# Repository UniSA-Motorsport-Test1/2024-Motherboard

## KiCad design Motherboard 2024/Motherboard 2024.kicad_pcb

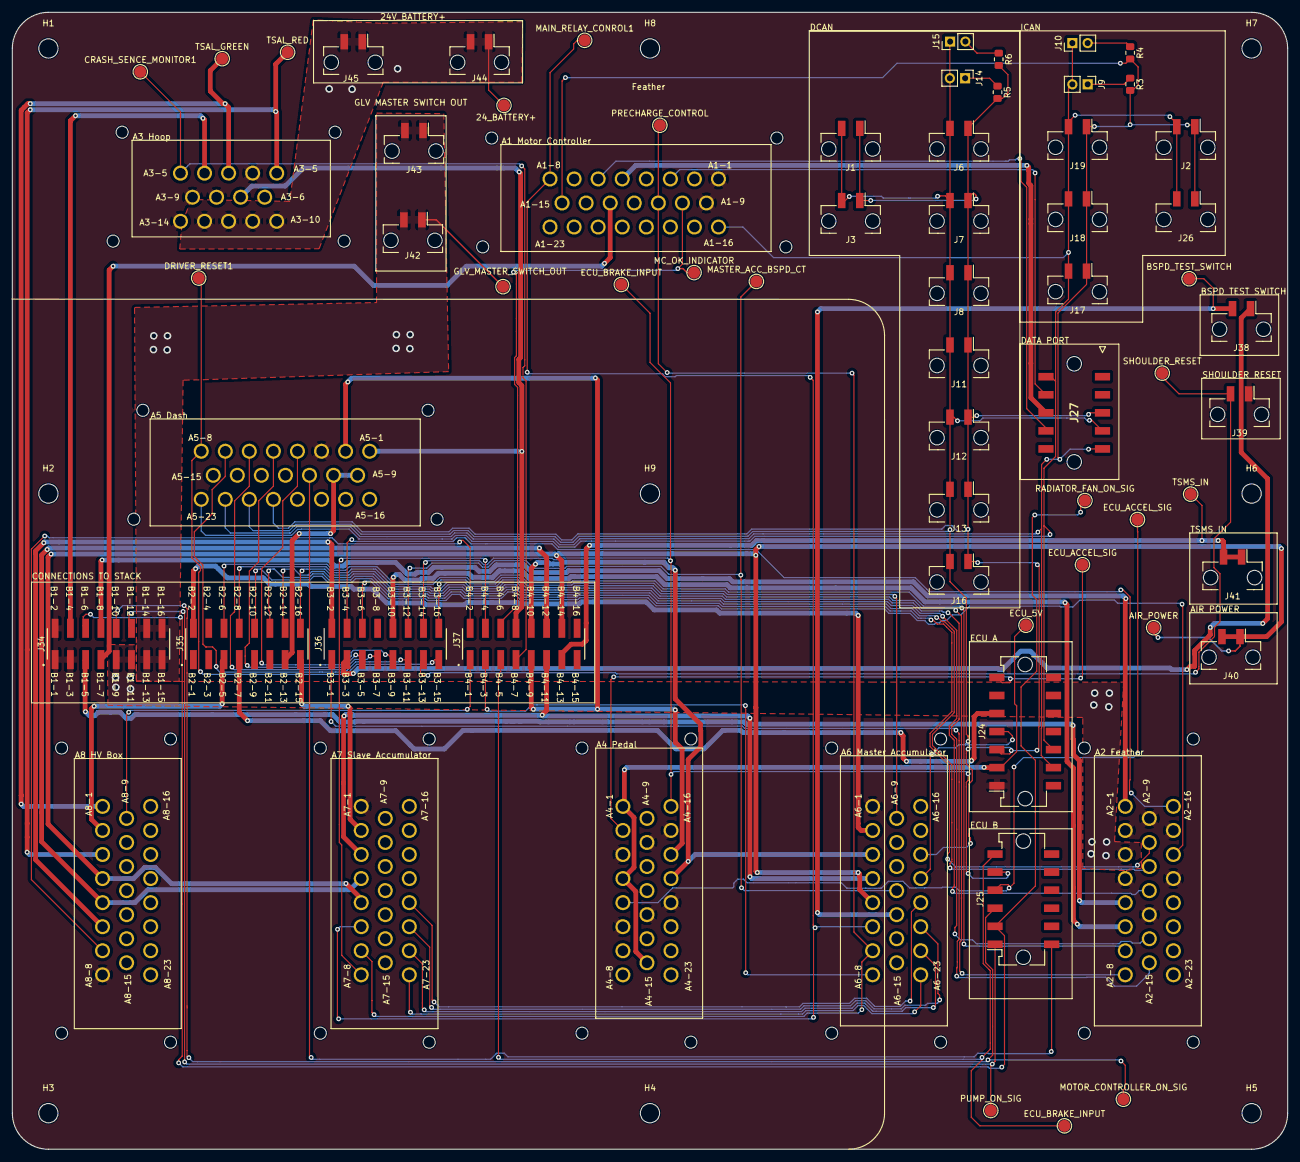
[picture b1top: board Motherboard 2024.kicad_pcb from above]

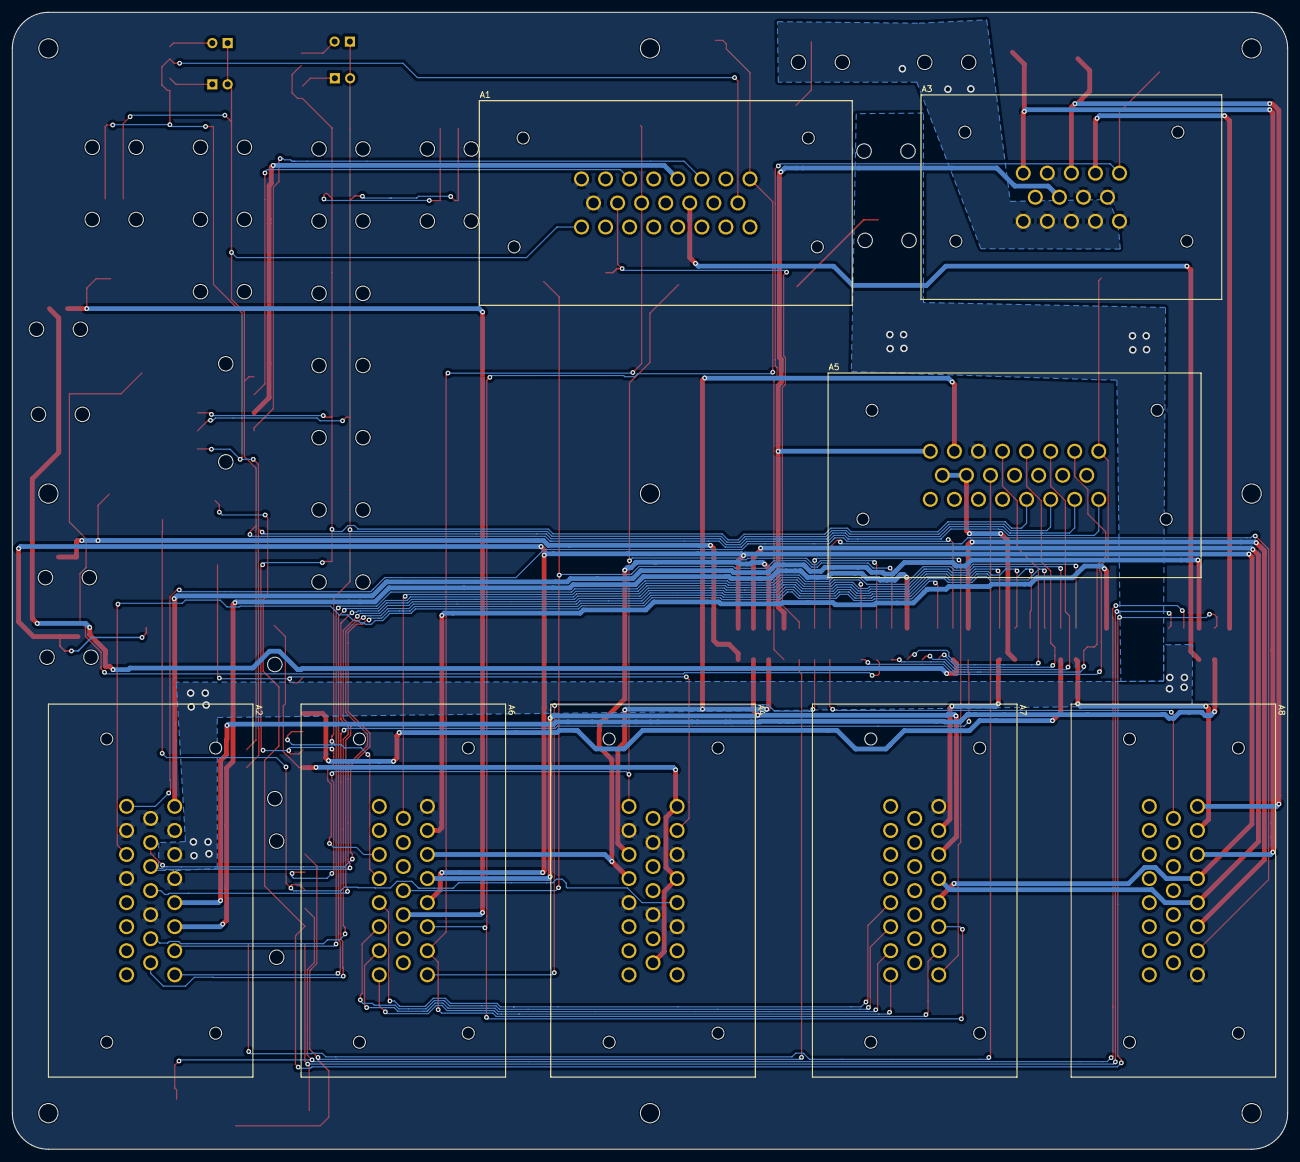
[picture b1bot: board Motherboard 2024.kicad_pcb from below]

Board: 2 copper layers, 212.0 x 189.0 mm, 76 parts (8 on the bottom side), 75 nets.

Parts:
24_BATTERY+: TestPoint; TestPoint_Pad_D2.0mm
A1: MOTOR CONTROLLER; AMPSEAL_3_ROW_23_PIN_VERTICAL
A2: Feathers; AMPSEAL_3_ROW_23_PIN_VERTICAL
A3: HOOP; AMPSEAL_3_ROW_14_PIN_VERTICAL
A4: PEDAL; AMPSEAL_3_ROW_23_PIN_VERTICAL
A5: DASH; AMPSEAL_3_ROW_23_PIN_VERTICAL
A6: MASTER ACCUMULATOR; AMPSEAL_3_ROW_23_PIN_VERTICAL
A7: SLAVE ACCUMULATOR; AMPSEAL_3_ROW_23_PIN_VERTICAL
A8: HV BOX; AMPSEAL_3_ROW_23_PIN_VERTICAL
AIR_POWER: TestPoint; TestPoint_Pad_D2.0mm
BSPD_TEST_SWITCH: TestPoint; TestPoint_Pad_D2.0mm
CRASH_SENCE_MONITOR1: TestPoint; TestPoint_Pad_D2.0mm
DRIVER_RESET1: TestPoint; TestPoint_Pad_D2.0mm
ECU_5V: TestPoint; TestPoint_Pad_D2.0mm
ECU_ACCEL_SIG: TestPoint; TestPoint_Pad_D2.0mm
ECU_ACCEL_SIG#2: TestPoint; TestPoint_Pad_D2.0mm
ECU_BRAKE_INPUT: TestPoint; TestPoint_Pad_D2.0mm
ECU_BRAKE_INPUT#2: TestPoint; TestPoint_Pad_D2.0mm
GLV_MASTER_SWITCH_OUT: TestPoint; TestPoint_Pad_D2.0mm
H1, H2, H3, H4, H5, H6, H7, H8, H9: MountingHole; MountingHole_3.2mm_M3
J1, J2, J3, J6, J7, J8, J11, J12, J13, J16, J17, J18, J19, J26: 43650-0221; Molex_Micro-Fit_3.0_43650-0221_1x02_P3.00mm_Vertical
J9, J10, J14, J15: Conn_01x02; PinHeader_1x02_P2.54mm_Vertical
J24: ECU_A; Molex_Micro-Fit_3.0_43045-1415_2x07_P3.00mm_Vertical
J25: ECU_B; Molex_Micro-Fit_3.0_43045-1215_2x06_P3.00mm_Vertical
J27: 43045-1015; MOLEX_43045-10YY_10PIN
J34, J35, J36, J37: HW-08-XX-XX-D-XXX-SM; SAMTEC_HW-08-XX-XX-D-XXX-SM
J38: BSPD_TEST_SWITCH; Molex_Micro-Fit_3.0_43650-0221_1x02_P3.00mm_Vertical
J39: SHOULDER_RESET; Molex_Micro-Fit_3.0_43650-0221_1x02_P3.00mm_Vertical
J40: AIR_POWER; Molex_Micro-Fit_3.0_43650-0221_1x02_P3.00mm_Vertical
J41: TSMS_IN; Molex_Micro-Fit_3.0_43650-0221_1x02_P3.00mm_Vertical
J42, J43: GLV_MASTER_SWITCH_OUT; Molex_Micro-Fit_3.0_43650-0221_1x02_P3.00mm_Vertical
J44, J45: 24V_BATTERY+; Molex_Micro-Fit_3.0_43650-0221_1x02_P3.00mm_Vertical
MAIN_RELAY_CONROL1: TestPoint; TestPoint_Pad_D2.0mm
MASTER_ACC_BSPD_CT: TestPoint; TestPoint_Pad_D2.0mm
MC_OK_INDICATOR: TestPoint; TestPoint_Pad_D2.0mm
MOTOR_CONTROLLER_ON_SIG: TestPoint; TestPoint_Pad_D2.0mm
PRECHARGE_CONTROL: TestPoint; TestPoint_Pad_D2.0mm
PUMP_ON_SIG: TestPoint; TestPoint_Pad_D2.0mm
R3, R4, R5, R6: 120R; 0805
RADIATOR_FAN_ON_SIG: TestPoint; TestPoint_Pad_D2.0mm
SHOULDER_RESET: TestPoint; TestPoint_Pad_D2.0mm
TSAL_GREEN: TestPoint; TestPoint_Pad_D2.0mm
TSAL_RED: TestPoint; TestPoint_Pad_D2.0mm
TSMS_IN: TestPoint; TestPoint_Pad_D2.0mm

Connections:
/24V_BATTERY+: 24_BATTERY+.1, A3.10, A3.11, A3.12, A3.13, J44.1, J44.2, J45.1, J45.2
/AIR_24V: A3.4, J34.4
/AIR_POWER: A6.5, A7.5, A8.4, AIR_POWER.1, J37.14, J40.1, J40.2
/BATT_CAN_HI: A6.21, A7.21
/BATT_CAN_LOW: A6.20, A7.20
/BOTS_IN: A4.18, A5.2, J37.9
/BOTS_OUT: A4.19, A6.3, J37.10
/BRAKE_LIGHT_12V: A2.5, J34.5
/BRAKE_LIGHT_GND: A2.6, J36.10
/BSPD_TEST_12V: J36.3, J38.1
/BSPD_TEST_SWITCH: A6.13, BSPD_TEST_SWITCH.1, J38.2
/CRASH_SENSOR_MONITOR: A3.5, CRASH_SENCE_MONITOR1.1, J37.7
/DASH_24V: A5.9, A5.10, J35.13
/DASH_AMS_LED: A5.7, J36.11
/DASH_BSPD_LED: A5.6, J36.7
/DASH_E-STOP_IN: A3.7, A5.1, J37.8
/DASH_IMD_LED: A5.4, J36.9
/DASH_PDOC_LED: A5.5, J36.5
/DISCHARGE_ENABLE_SIGNAL: A6.9, J36.16
/DRIVER_RESET_IN: A5.8, DRIVER_RESET1.1, J36.15
/D_CAN_HI: A5.21, A6.19, J1.2, J3.2, J6.2, J7.2, J8.2, J11.2, J12.2, J13.2, J14.2, J15.1, J16.2, J24.4, J27.4
/D_CAN_LOW: A5.20, A6.18, J1.1, J3.1, J6.1, J7.1, J8.1, J11.1, J12.1, J13.1, J16.1, J24.3, J27.3, R5.2, R6.2
/ECU_5V_POWER_SENSOR_SUPPLY: A4.1, A4.4, A4.15, ECU_5V.1, J24.2
/ECU_24V: J24.5, J35.7
/ECU_ACCELERATOR_SIGNAL_1: A4.2, ECU_ACCEL_SIG#2.1, J24.7
/ECU_ACCELERATOR_SIGNAL_2: A4.5, ECU_ACCEL_SIG.1, J25.4
/ECU_BRAKE_INPUT: A4.16, ECU_BRAKE_INPUT#2.1, J25.5, J36.14
/ECU_OK: ECU_BRAKE_INPUT.1, J25.6, J37.5
/GLV_MASTER_SWITCH_OUT: GLV_MASTER_SWITCH_OUT.1, J34.13, J34.14, J34.15, J34.16, J42.1, J42.2, J43.1, J43.2
/GND: A1.1, A1.9, A2.2, A2.4, A2.9, A2.13, A2.17, A2.19, A3.2, A3.8, A3.9, A3.14, A4.3, A4.6, A4.10, A4.13, A4.17, A4.20, A5.3, A6.1, A7.1, A8.8, J24.1, J34.1, J34.2, J34.3, J39.1
/HV_BOX_24V: A8.2, J35.5
/HV_BOX_GREEN: A3.3, A8.1, TSAL_GREEN.1
/HV_BOX_HVD_INT_IN: A7.4, A8.5, J37.12
/HV_BOX_HVD_INT_OUT: A8.6, J36.2
/HV_BOX_IMD_OK: A8.9, J37.1
/HV_BOX_PDOC_OK: A8.7, J37.2
/HV_BOX_RED: A3.1, A8.3, TSAL_RED.1
/I_CAN_HI: A1.16, A5.23, J2.2, J9.2, J10.1, J17.2, J18.2, J19.2, J24.10, J26.2, J27.6
/I_CAN_LOW: A1.15, A5.22, J2.1, J17.1, J18.1, J19.1, J24.9, J26.1, J27.5, R3.2, R4.2
/MAIN_RELAY_CONTROL: A1.8, A6.6, A7.6, MAIN_RELAY_CONROL1.1
/MASTER_ACC_24V: A6.2, J35.2
/MASTER_ACC_BSPD_CT: A6.12, J36.12, MASTER_ACC_BSPD_CT.1
/MASTER_ACC_HV_INT_OUT: A6.4, A7.3, J37.11
/MASTER_ACC_PDOC_OK: A6.8, J37.3
/MC_12V: A1.13, J34.7
/MC_OK_INDICATOR: A1.10, J37.6, MC_OK_INDICATOR.1
/MC_RS232_GND: A1.5, J27.8
/MC_RS232_RXD: A1.6, J27.9
/MC_RS232_TXD: A1.3, J27.7
/MOTOR_CONTROLLER_ON_SIGNAL: J25.3, J34.10, MOTOR_CONTROLLER_ON_SIG.1
/PRECHARGE_CONTROL: A1.11, A6.7, A7.7, PRECHARGE_CONTROL.1
/PRESSURE/TEMP_SENSOR_1_5V: A2.8, J35.8
/PRESSURE/TEMP_SENSOR_1_PRESSURE: A2.7, J35.6
/PRESSURE/TEMP_SENSOR_1_TEMP: A2.10, J35.10
/PRESSURE/TEMP_SENSOR_2_5V: A2.12, J35.14
/PRESSURE/TEMP_SENSOR_2_PRESSURE: A2.11, J35.12
/PRESSURE/TEMP_SENSOR_2_TEMP: A2.14, J35.16
/PRESSURE/TEMP_SENSOR_3_5V: A2.16, J36.4
/PRESSURE/TEMP_SENSOR_3_PRESSURE: A2.15, J36.1
/PRESSURE/TEMP_SENSOR_3_TEMP: A2.18, J36.6
/PUMP_ON_SIGNAL: J25.1, J34.12, PUMP_ON_SIG.1
/RADIATOR_FAN_24V: A2.1, J34.8
/RADIATOR_FAN_ON_SIGNAL: J25.2, J34.6, RADIATOR_FAN_ON_SIG.1
/RADIATOR_WATER_PUMP_24V: A2.3, J34.9, J34.11
/REMOTE+: A6.23, A7.23
/REMOTE-: A6.22, A7.22
/RTS_SPEAKER-: A5.11, J25.7
/SAFTEY_OUT: J37.13, J41.1, J41.2, TSMS_IN.1
/SHOULDER_RESET: J36.13, J39.2, SHOULDER_RESET.1
/SLAVE_ACC_24V: A7.2, J35.15
/SLAVE_ACC_PDOC_OK: A7.8, J37.4
unnamed: J9.1, R3.1
unnamed: J10.2, R4.1
unnamed: J14.1, R5.1
unnamed: J15.2, R6.1

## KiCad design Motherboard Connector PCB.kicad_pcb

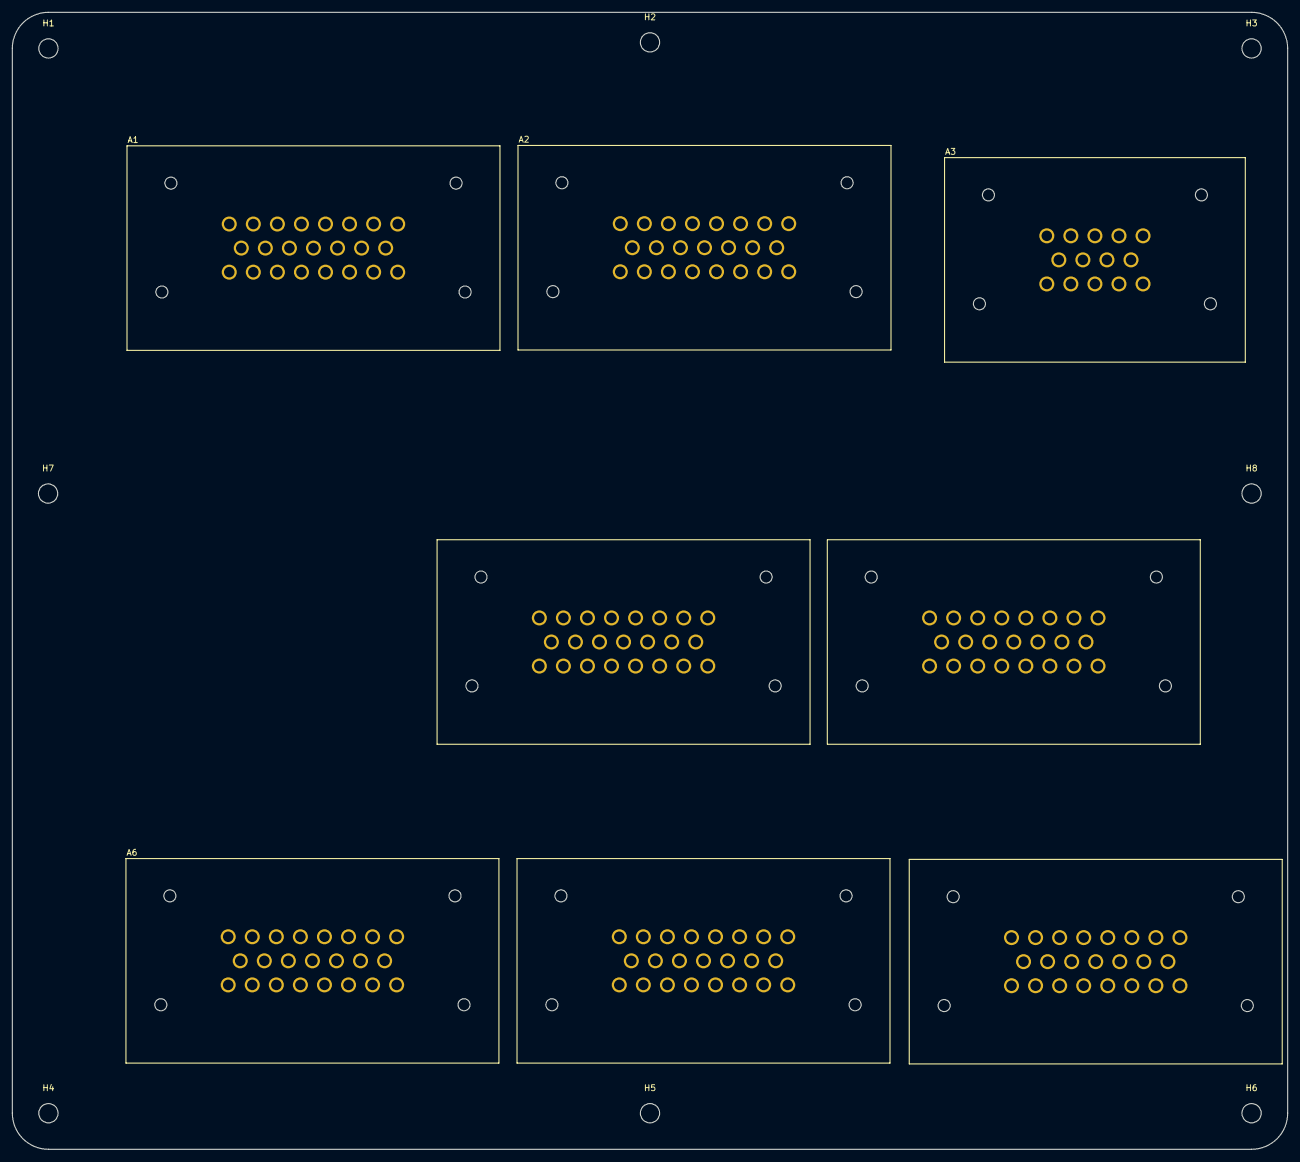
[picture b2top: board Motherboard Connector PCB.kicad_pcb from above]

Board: 2 copper layers, 212.0 x 189.0 mm, 16 parts (0 on the bottom side), 12 nets, no tracks yet.

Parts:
A1: MOTOR CONTROLLER; AMPSEAL_3_ROW_23_PIN_VERTICAL
A2: Feathers; AMPSEAL_3_ROW_23_PIN_VERTICAL
A3: HOOP; AMPSEAL_3_ROW_14_PIN_VERTICAL
A4: PEDAL; AMPSEAL_3_ROW_23_PIN_VERTICAL
A5: DASH; AMPSEAL_3_ROW_23_PIN_VERTICAL
A6: MASTER ACCUMULATOR; AMPSEAL_3_ROW_23_PIN_VERTICAL
A7: SLAVE ACCUMULATOR; AMPSEAL_3_ROW_23_PIN_VERTICAL
A8: HV BOX; AMPSEAL_3_ROW_23_PIN_VERTICAL
H1, H2, H3, H4, H5, H6, H7, H8: MountingHole; MountingHole_3.2mm_M3

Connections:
/24V_BATTERY+: A1.1, A1.9, A2.2, A2.4, A2.9, A2.13, A2.17, A2.19, A3.2, A3.8, A3.9, A3.10, A3.11, A3.12, A3.13, A3.14, A4.3, A4.6, A4.10, A4.13, A4.17, A4.20, A5.3, A6.1, A7.1, A8.8
/AIR_POWER: A6.5, A7.5, A8.4
/BATT_CAN_HI: A6.21, A7.21
/BATT_CAN_LOW: A6.20, A7.20
/DASH_24V: A5.9, A5.10
/D_CAN_HI: A5.21, A6.19
/D_CAN_LOW: A5.20, A6.18
/ECU_5V_POWER_SENSOR_SUPPLY: A4.1, A4.4, A4.15
/MAIN_RELAY_CONTROL: A1.8, A7.6
/PRECHARGE_CONTROL: A1.11, A7.7
/REMOTE+: A6.23, A7.23
/REMOTE-: A6.22, A7.22

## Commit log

2024-04-23 final motherboard Before design check
2024-09-12 Updated 12 Sep
